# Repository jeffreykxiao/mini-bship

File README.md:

# Mini Battleship

船舶解体計画

## Possible Layouts

## Why?

The build quality of the 5576-001 is pretty terrible. The IBM badge is meh, the indicator lights section is a boring cutout with a crappy overlay that invariably gets damaged, and overall neither case seems to be particularly sturdy - despite being heavier than the P70, it seems to be just as, if not more, flexy. Maybe it's just a product of the post-bubble economy, but 40k JPY for something with this construction feels wrong. If the keyboard had been like a Model M with a steel backplate, I would have left it alone, but as it stands, the board comes with uniquely fun switches and great two-piece Alps dyesub keycaps. 

## APS Notes

Alps Plate Springs are amazing switches that feel like tiny buckling springs even though they are a stacked spring design. The PCB-mount ones from the -001 are especially hilarious (6 pins!) but their plate-mount cousins from the -JA1 seem to be fine as well. I've noticed they are not quite the same in terms of construction as well. Though you can swap the top housings, stems and stem springs, and plate springs, they don't quite sound or feel the same once swapped. For example, swapping a plate-mount plate spring into a PCB-mount causes the click to become more high-pitched and the switch feels a bit "loose" for lack of better words. The top housings also appear to be made of different plastics as they are differently colored.

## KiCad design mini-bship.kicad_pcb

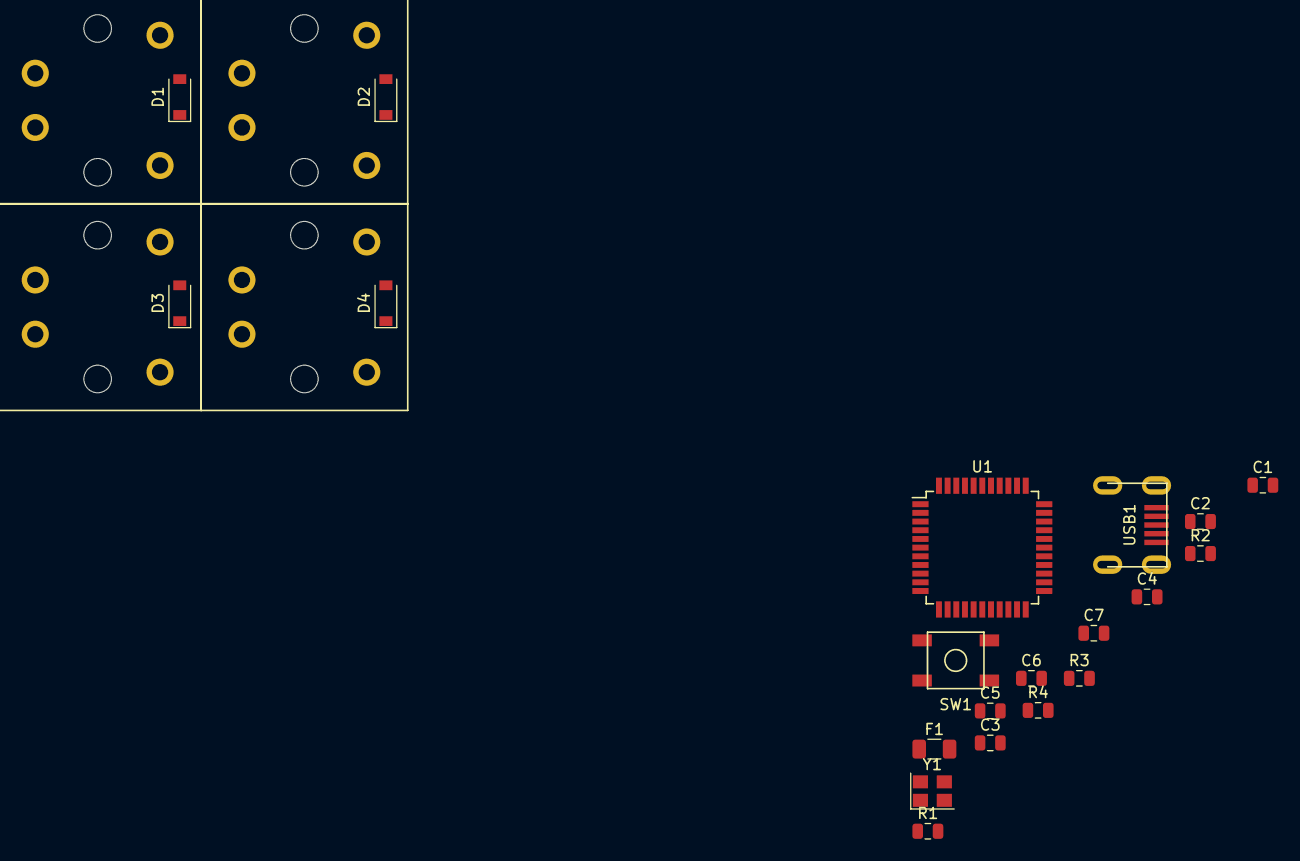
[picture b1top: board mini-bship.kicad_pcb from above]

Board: 2 copper layers, 24 parts (0 on the bottom side), 20 nets, no tracks yet.

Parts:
C1, C2: 22pF; C_0805_2012Metric
C3: 1uF; C_0805_2012Metric
C4, C5, C6, C7: 0.1uF; C_0805_2012Metric
D1, D2, D3, D4: D_Small; D_SOD-123
F1: 500mA; Fuse_1206_3216Metric
MX1, MX2, MX3, MX4: MX-NoLED; ALPS_PLATE_SPRING
R1, R4: 10k; R_0805_2012Metric
R2, R3: 22; R_0805_2012Metric
SW1: SW_Push; SKQG-1155865
U1: ATmega32U4-AU; TQFP-44_10x10mm_P0.8mm
USB1: Molex-0548190589
Y1: 16MHz; Crystal_SMD_3225-4Pin_3.2x2.5mm

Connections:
+5V: C4.1, C5.1, C6.1, C7.1, F1.1, R1.1, U1.2, U1.7, U1.14, U1.24, U1.34, U1.44
COL0: MX1.1, MX3.1
COL1: MX2.1, MX4.1
D+: R2.2, USB1.3
D-: R3.2, USB1.4
GND: C1.2, C2.2, C3.2, C4.2, C5.2, C6.2, C7.2, R4.1, SW1.1, U1.5, U1.15, U1.23, U1.35, U1.43, USB1.1, Y1.2, Y1.4
unnamed: C1.1, U1.17, Y1.1
unnamed: C2.1, U1.16, Y1.3
unnamed: C3.1, U1.6
unnamed: D1.2, MX1.2
unnamed: D2.2, MX2.2
unnamed: D3.2, MX3.2
unnamed: D4.2, MX4.2
unnamed: R1.2, SW1.2, U1.13
unnamed: R2.1, U1.4
unnamed: R3.1, U1.3
unnamed: R4.2, U1.33
ROW0: D1.1, D2.1
ROW1: D3.1, D4.1
VCC: F1.2, USB1.5

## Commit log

2019-07-28 Initial commit - add standard kicad gitignore
2019-07-28 Add boilerplate readme
2019-07-28 Default project files
2019-07-28 Add submodules (2x ai03, 1x hasu)
2019-07-28 Add initial layout idea created in KLE
2019-07-28 Update readme with initial thoughts
2019-07-28 Switch to PNG since SVG has no legends
2019-07-28 Add USB-C Parts submodule
2019-07-28 Add all the new layout ideas, update readme
2019-07-28 Update layout formatting
2019-07-28 Added kicad lib links
2019-07-28 Add basic schematic boilerplate, up to guide p4
2019-07-29 Add part from snacksthecat for plate mount if need
2019-07-29 Slow progress, got started on pcb
